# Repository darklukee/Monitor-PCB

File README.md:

Monitor-PCB
===========

PCB design for Monitor

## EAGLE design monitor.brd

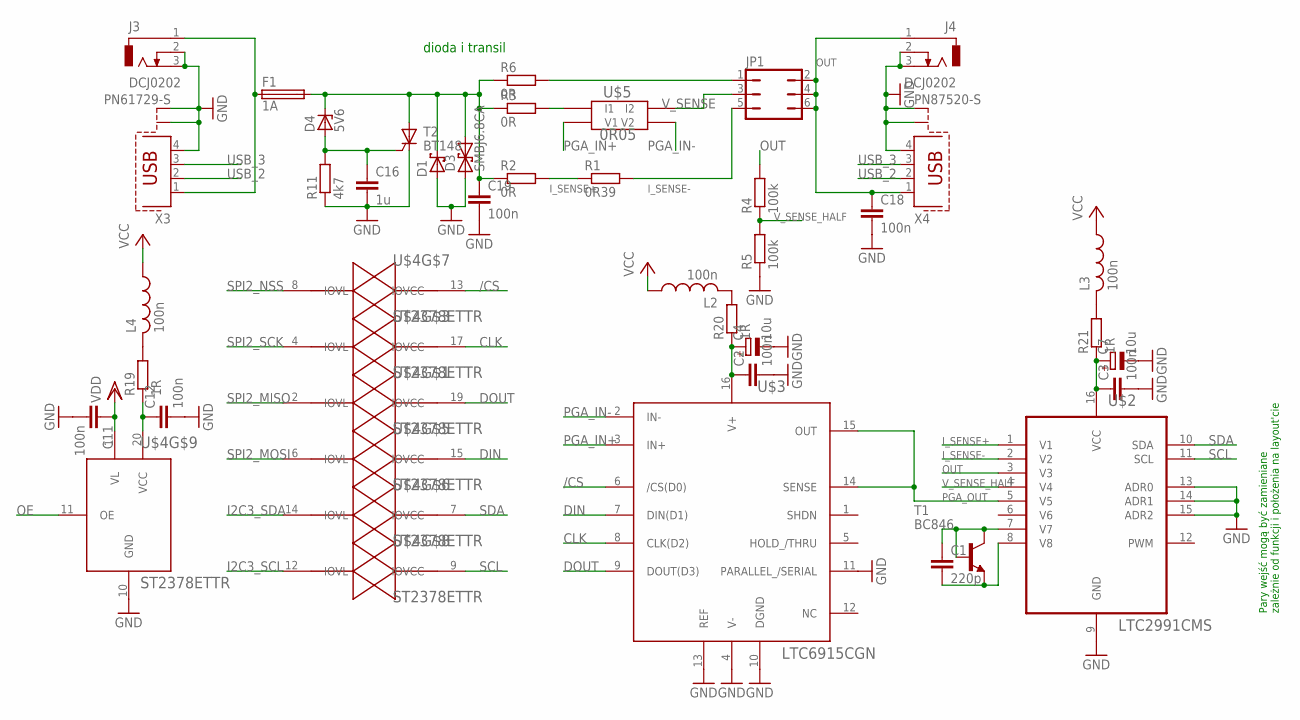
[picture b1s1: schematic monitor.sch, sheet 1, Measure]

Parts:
C1: 220p; C0805
C2, C3, C11, C12, C18, C19: 100n; C0603
C4, C7: 10u; SMC_A
C16: 1u; C0805
D1: SCHOTTKY-DIODESMD; SMB
D3: SMBJ6.8CA; SMB
D4: 5V6; SOD80C
F1: 1A; R1206
J3, J4: DCJ0202
JP1: JP3Q
L2, L3, L4: 100n; R0603
R1: 0R39; 0207/7
R2, R3, R6: 0R; R0805
R4, R5: 100k; R0805
R11: 4k7; R0805
R19, R20, R21: 1R; R0603
T1: BC846; SOT23
T2: BT148; SOT223
U$2: LTC2991CMS; SOP50P490X110-16N
U$3: LTC6915CGN; SOP65P640X120-16N
U$4: ST2378ETTR; TSSOP20
U$5: 0R05; LVK12
X3: PN61729-S
X4: PN87520-S

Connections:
/CS: U$3.6 (/CS(D0)), U$4.13 (IOVCC)
CLK: U$3.8 (CLK(D2)), U$4.17 (IOVCC)
DIN: U$3.7 (DIN(D1)), U$4.15 (IOVCC)
DOUT: U$3.9 (DOUT(D3)), U$4.19 (IOVCC)
GND: C2.2, C3.2, C4.-, C7.-, C11.2, C12.2, C16.2, C18.2, C19.2, D1.A, D3.A (1), J3.2, J3.3, J4.2, J4.3, R5.1, R11.1, T2.1 (C), U$2.9 (GND), U$2.13 (ADR0), U$2.14 (ADR1), U$2.15 (ADR2), U$3.4 (V-), U$3.10 (DGND), U$3.11 (PARALLEL_/SERIAL), U$3.13 (REF), U$4.10 (GND), X3.4, X3.S1, X3.S2, X4.4, X4.S1, X4.S2; also elsewhere on the board
I2C3_SCL: U$4.12 (IOVL); also elsewhere on the board
I2C3_SDA: U$4.14 (IOVL); also elsewhere on the board
IN: F1.1, J3.1, X3.1
I_SENSE+: R1.1, R2.2, U$2.1 (V1)
I_SENSE-: JP1.5, R1.2, U$2.2 (V2)
unnamed: R3.2, U$5.P$3 (I1)
unnamed: JP1.1, R6.2
unnamed: C19.1, D1.C, D3.C (2), D4.C, F1.2, R2.1, R3.1, R6.1, T2.2 (A)
unnamed: C1.1, T1.1 (B), T1.3 (C), U$2.7 (V7)
unnamed: C1.2, T1.2 (E), U$2.8 (V8)
unnamed: C16.1, D4.A, R11.2, T2.3 (G)
unnamed: C12.1, R19.1, U$4.20 (VCC)
unnamed: L4.2, R19.2
unnamed: C2.1, C4.+, R20.1, U$3.16 (V+)
unnamed: C3.1, C7.+, R21.1, U$2.16 (VCC)
unnamed: L2.2, R20.2
unnamed: L3.2, R21.2
OE: U$4.11 (OE); also elsewhere on the board
OUT: C18.1, J4.1, JP1.2, JP1.4, JP1.6, R4.2, U$2.3 (V3), X4.1
PGA_IN+: U$3.3 (IN+), U$5.P$4 (V1)
PGA_IN-: U$3.2 (IN-), U$5.P$1 (V2)
PGA_OUT: U$2.5 (V5), U$3.14 (SENSE), U$3.15 (OUT)
SCL: U$2.11 (SCL), U$4.9 (IOVCC)
SDA: U$2.10 (SDA), U$4.7 (IOVCC)
SPI2_MISO: U$4.2 (IOVL); also elsewhere on the board
SPI2_MOSI: U$4.6 (IOVL); also elsewhere on the board
SPI2_NSS: U$4.8 (IOVL); also elsewhere on the board
SPI2_SCK: U$4.4 (IOVL); also elsewhere on the board
USB_2: X3.2, X4.2
USB_3: X3.3, X4.3
VCC: L2.1, L3.1, L4.1; also elsewhere on the board
VDD: C11.1, U$4.1 (VL); also elsewhere on the board
V_SENSE: JP1.3, U$5.P$2 (I2)
V_SENSE_HALF: R4.1, R5.2, U$2.4 (V4)

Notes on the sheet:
dioda i transil
Pary wejść mogą być zamieniane zależnie od funkcji i położenia na layout'cie

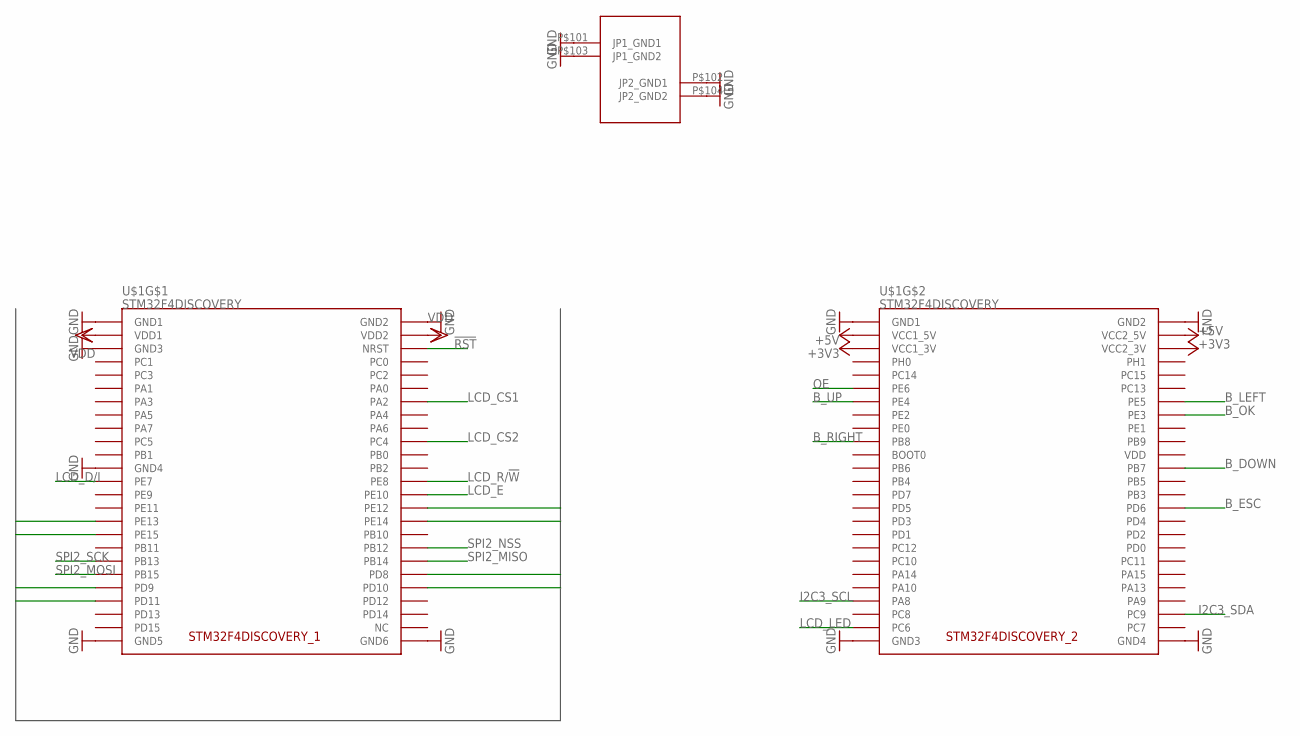
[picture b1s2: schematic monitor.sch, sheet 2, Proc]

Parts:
U$1: STM32F4DISCOVERY

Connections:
!RST: U$1.P$6 (NRST); also elsewhere on the board
+3V3: U$1.P$55 (VCC1_3V), U$1.P$56 (VCC2_3V)
+5V: U$1.P$53 (VCC1_5V), U$1.P$54 (VCC2_5V); also elsewhere on the board
B_DOWN: U$1.P$74 (PB7); also elsewhere on the board
B_ESC: U$1.P$80 (PD6); also elsewhere on the board
B_LEFT: U$1.P$64 (PE5); also elsewhere on the board
B_OK: U$1.P$66 (PE3); also elsewhere on the board
B_RIGHT: U$1.P$69 (PB8); also elsewhere on the board
B_UP: U$1.P$63 (PE4); also elsewhere on the board
GND: U$1.P$1 (GND1), U$1.P$2 (GND2), U$1.P$5 (GND3), U$1.P$23 (GND4), U$1.P$49 (GND5), U$1.P$50 (GND6), U$1.P$51 (GND1), U$1.P$52 (GND2), U$1.P$99 (GND3), U$1.P$100 (GND4), U$1.P$101 (JP1_GND1), U$1.P$102 (JP2_GND1), U$1.P$103 (JP1_GND2), U$1.P$104 (JP2_GND2); also elsewhere on the board
I2C3_SCL: U$1.P$93 (PA8); also elsewhere on the board
I2C3_SDA: U$1.P$96 (PC9); also elsewhere on the board
LCD_CS1: U$1.P$14 (PA2); also elsewhere on the board
LCD_CS2: U$1.P$20 (PC4); also elsewhere on the board
LCD_D0: U$1.P$30 (PE12); also elsewhere on the board
LCD_D1: U$1.P$31 (PE13); also elsewhere on the board
LCD_D2: U$1.P$32 (PE14); also elsewhere on the board
LCD_D3: U$1.P$33 (PE15); also elsewhere on the board
LCD_D4: U$1.P$40 (PD8); also elsewhere on the board
LCD_D5: U$1.P$41 (PD9); also elsewhere on the board
LCD_D6: U$1.P$42 (PD10); also elsewhere on the board
LCD_D7: U$1.P$43 (PD11); also elsewhere on the board
LCD_D/I: U$1.P$25 (PE7); also elsewhere on the board
LCD_E: U$1.P$28 (PE10); also elsewhere on the board
LCD_LED: U$1.P$97 (PC6); also elsewhere on the board
LCD_R/!W: U$1.P$26 (PE8); also elsewhere on the board
OE: U$1.P$61 (PE6); also elsewhere on the board
SPI2_MISO: U$1.P$38 (PB14); also elsewhere on the board
SPI2_MOSI: U$1.P$39 (PB15); also elsewhere on the board
SPI2_NSS: U$1.P$36 (PB12); also elsewhere on the board
SPI2_SCK: U$1.P$37 (PB13); also elsewhere on the board
VDD: U$1.P$3 (VDD1), U$1.P$4 (VDD2); also elsewhere on the board

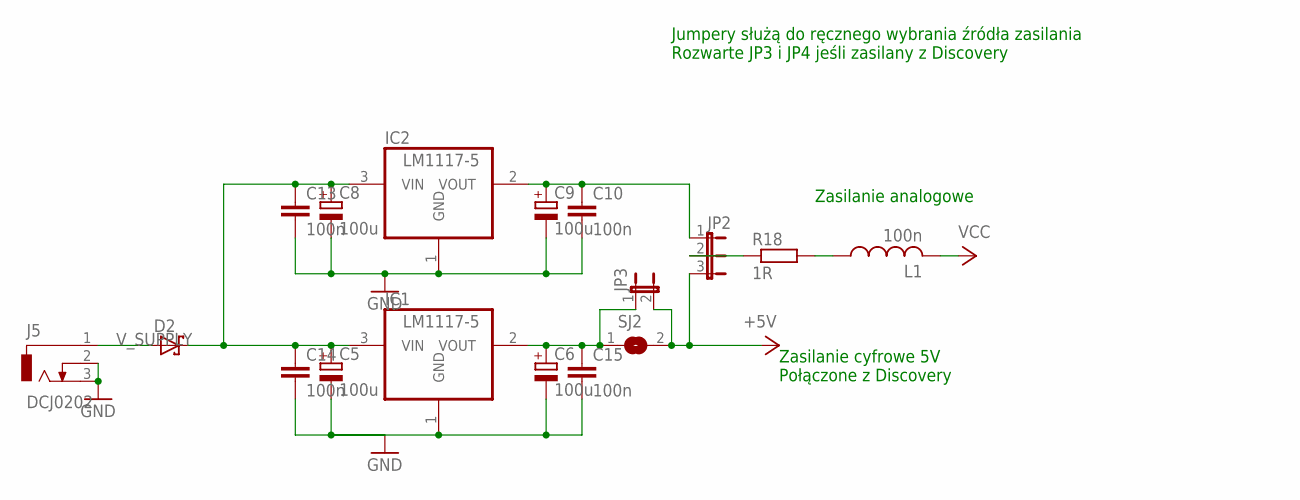
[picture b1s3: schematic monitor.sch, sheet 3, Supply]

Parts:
C5, C6, C8, C9: 100u; SMC_B
C10, C13, C14, C15: 100n; C0603
D2: SCHOTTKY-DIODESMD; SMB
IC1, IC2: LM1117-5; SOT223
J5: DCJ0202
JP2: JP2E; JP2
JP3: JP1E; JP1
L1: 100n; R0603
R18: 1R; R0603
SJ2: SJ

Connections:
+5V: JP2.3, JP3.2, SJ2.2; also elsewhere on the board
GND: C5.-, C6.-, C8.-, C9.-, C10.2, C13.2, C14.2, C15.2, IC1.1 (GND), IC2.1 (GND), J5.2, J5.3; also elsewhere on the board
unnamed: C6.+, C15.1, IC1.2 (VOUT), JP3.1, SJ2.1
unnamed: C9.+, C10.1, IC2.2 (VOUT), JP2.1
unnamed: D2.A, J5.1
unnamed: L1.1, R18.2
unnamed: JP2.2, R18.1
VCC: L1.2; also elsewhere on the board
V_SUPPLY: C5.+, C8.+, C13.1, C14.1, D2.C, IC1.3 (VIN), IC2.3 (VIN)

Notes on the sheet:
Zasilanie analogowe
Zasilanie cyfrowe 5V Połączone z Discovery
Jumpery służą do ręcznego wybrania źródła zasilania Rozwarte JP3 i JP4 jeśli zasilany z Discovery

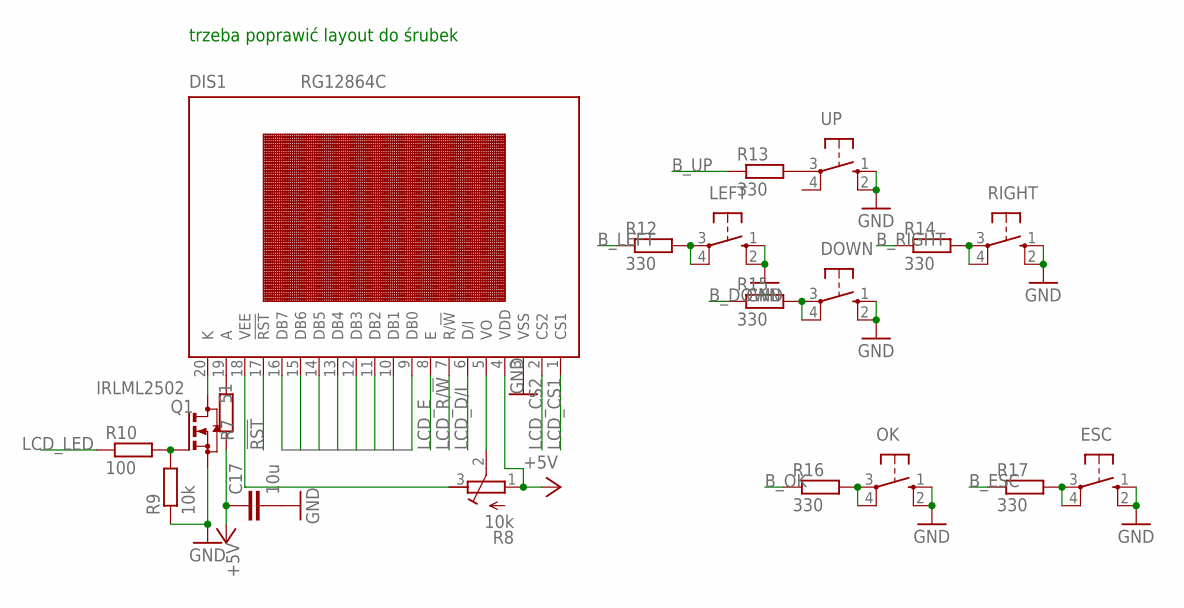
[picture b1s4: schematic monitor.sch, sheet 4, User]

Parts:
C17: 10u; C1206
DIS1: RG12864C
DOWN: 40-XX; B3F-40XX
ESC: 40-XX; B3F-40XX
LEFT: 40-XX; B3F-40XX
OK: 40-XX; B3F-40XX
Q1: IRLML2502; SOT23
R7: 51; R1206
R8: 10k; RTRIMTS53YJ
R9: 10k; R0805
R10: 100; R0805
R12, R13, R14, R15, R16, R17: 330; R0805
RIGHT: 40-XX; B3F-40XX
UP: 40-XX; B3F-40XX

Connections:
!RST: DIS1.17 (!RST); also elsewhere on the board
+5V: C17.1, DIS1.4 (VDD), R7.1, R8.1 (A); also elsewhere on the board
B_DOWN: R15.1; also elsewhere on the board
B_ESC: R17.1; also elsewhere on the board
B_LEFT: R12.1; also elsewhere on the board
B_OK: R16.1; also elsewhere on the board
B_RIGHT: R14.1; also elsewhere on the board
B_UP: R13.1; also elsewhere on the board
GND: C17.2, DIS1.3 (VSS), DOWN.1 (S), DOWN.2 (S1), ESC.1 (S), ESC.2 (S1), LEFT.1 (S), LEFT.2 (S1), OK.1 (S), OK.2 (S1), Q1.2 (S), R9.1, RIGHT.1 (S), RIGHT.2 (S1), UP.1 (S), UP.2 (S1); also elsewhere on the board
LCD_CS1: DIS1.1 (CS1); also elsewhere on the board
LCD_CS2: DIS1.2 (CS2); also elsewhere on the board
LCD_D0: DIS1.9 (DB0); also elsewhere on the board
LCD_D1: DIS1.10 (DB1); also elsewhere on the board
LCD_D2: DIS1.11 (DB2); also elsewhere on the board
LCD_D3: DIS1.12 (DB3); also elsewhere on the board
LCD_D4: DIS1.13 (DB4); also elsewhere on the board
LCD_D5: DIS1.14 (DB5); also elsewhere on the board
LCD_D6: DIS1.15 (DB6); also elsewhere on the board
LCD_D7: DIS1.16 (DB7); also elsewhere on the board
LCD_D/I: DIS1.6 (D/I); also elsewhere on the board
LCD_E: DIS1.8 (E); also elsewhere on the board
LCD_LED: R10.1; also elsewhere on the board
LCD_R/!W: DIS1.7 (R/!W); also elsewhere on the board
unnamed: DIS1.19 (A), R7.2
unnamed: DIS1.18 (VEE), R8.3 (E)
unnamed: DIS1.5 (VO), R8.2 (S)
unnamed: LEFT.3, LEFT.4 (P1), R12.2
unnamed: DIS1.20 (K), Q1.3 (D)
unnamed: Q1.1 (G), R9.2, R10.2
unnamed: R13.2, UP.3
unnamed: R14.2, RIGHT.3, RIGHT.4 (P1)
unnamed: DOWN.3, DOWN.4 (P1), R15.2
unnamed: ESC.3, ESC.4 (P1), R17.2
unnamed: OK.3, OK.4 (P1), R16.2

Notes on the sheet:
trzeba poprawić layout do śrubek

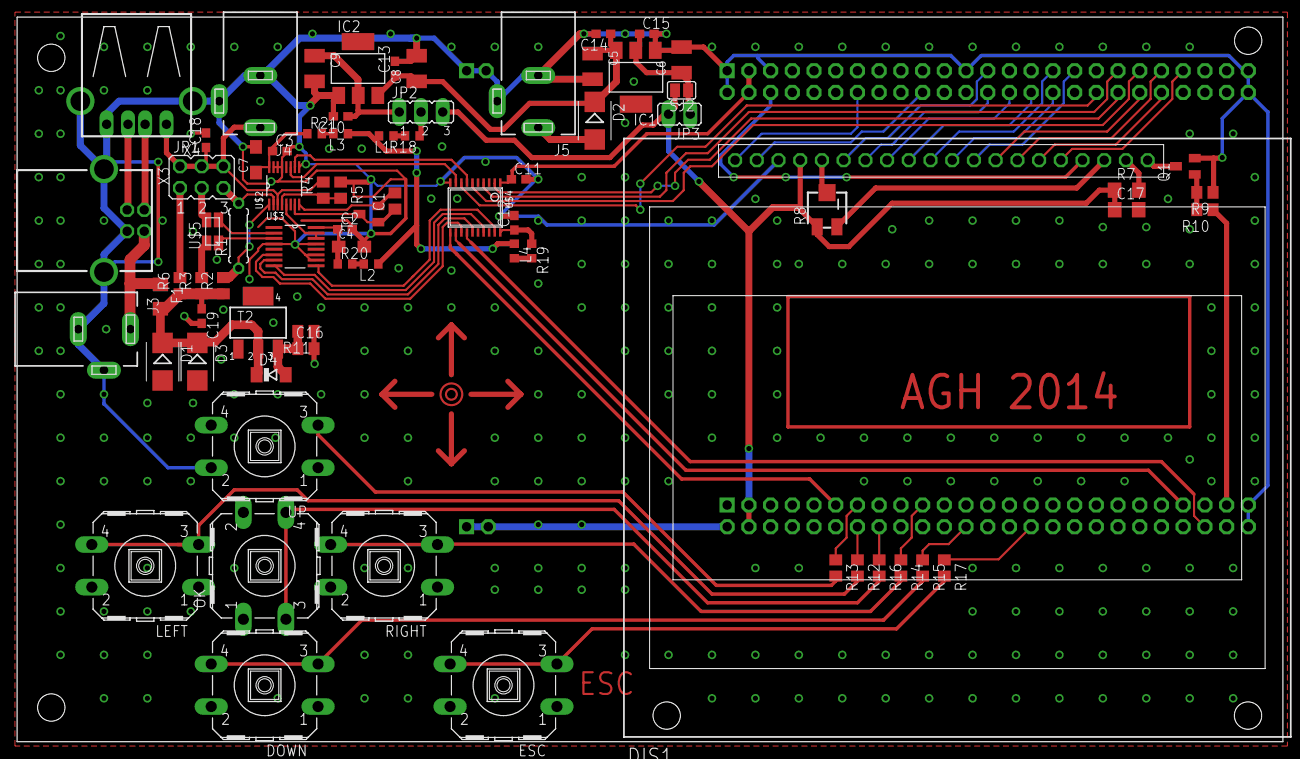
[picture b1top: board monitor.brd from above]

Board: 2 copper layers, 148.1 x 84.8 mm, 75 parts (1 on the bottom side), 79 nets.

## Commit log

2013-08-15 gitignore for CadSoft Eagle
2013-08-15 init commit
2013-08-15 CadSoft Eagle .gitignore
2013-08-15 SPI to PGA
2013-08-15 All chips connected
2013-08-16 All connected (not routed), updated STM32F4Discovery layout
2013-08-17 All routed, drill diameter increased
2013-08-24 Added inductors on analog supply. Rerouted some signals.
2013-08-24 Extra vias
2013-08-24 minor improvements
2013-08-24 drill sizes
2013-08-25 Ground plane on top layer
2013-08-26 vias
2014-06-09 condensators, minor layout changes
